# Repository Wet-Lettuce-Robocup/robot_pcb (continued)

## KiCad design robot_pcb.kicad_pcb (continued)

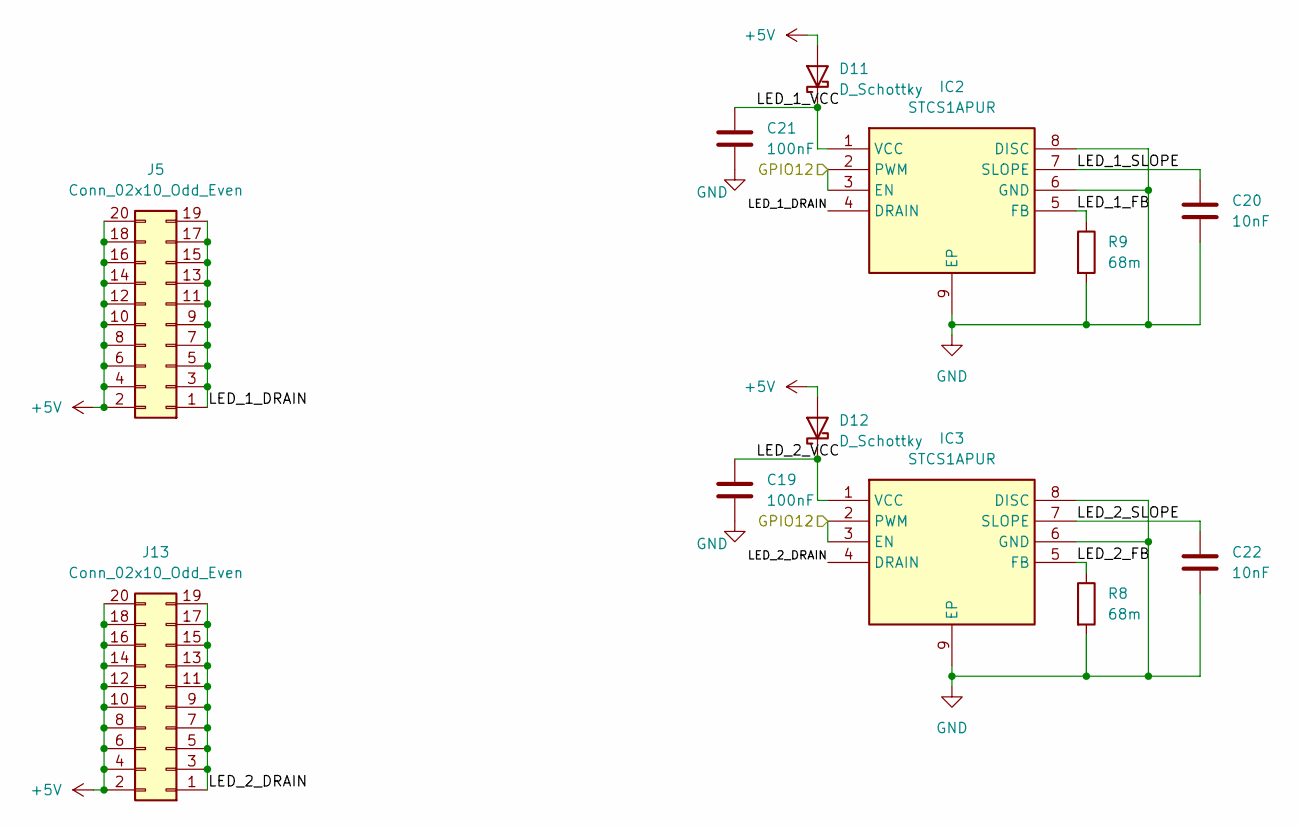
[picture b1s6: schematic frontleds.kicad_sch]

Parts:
C19, C21: 100nF; C_0402_1005Metric; LCSC C307331
C20, C22: 10nF; C_0402_1005Metric; LCSC C15195
D11, D12: D_Schottky; D_SOD-123; LCSC C83528
IC2, IC3: STCS1APUR; SON50P300X300X100-9N-D; Mouser Part Number 511-STCS1APUR
J5, J13: Conn_02x10_Odd_Even; Samtec_HSEC8-110-01-X-DV-A_2x10_P0.8mm_Socket_AlignmentPins; LCSC C4572809
R8, R9: 68m; R_0402_1005Metric; LCSC C728416

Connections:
+5V: D11.2 (A), D12.2 (A), J5.2, J5.4, J5.6, J5.8, J5.10, J5.12, J5.14, J5.16, J5.18, J5.20, J13.2, J13.4, J13.6, J13.8, J13.10, J13.12, J13.14, J13.16, J13.18, J13.20; also elsewhere on the board
/Front LEDs/GPIO12: IC2.2 (PWM), IC2.3 (EN), IC3.2 (PWM), IC3.3 (EN); also elsewhere on the board
/Front LEDs/LED_1_DRAIN: IC2.4 (DRAIN), J5.1, J5.3, J5.5, J5.7, J5.9, J5.11, J5.13, J5.15, J5.17, J5.19
/Front LEDs/LED_1_FB: IC2.5 (FB), R9.1
/Front LEDs/LED_1_SLOPE: C20.2, IC2.7 (SLOPE)
/Front LEDs/LED_1_VCC: C21.1, D11.1 (K), IC2.1 (VCC)
/Front LEDs/LED_2_DRAIN: IC3.4 (DRAIN), J13.1, J13.3, J13.5, J13.7, J13.9, J13.11, J13.13, J13.15, J13.17, J13.19
/Front LEDs/LED_2_FB: IC3.5 (FB), R8.1
/Front LEDs/LED_2_SLOPE: C22.1, IC3.7 (SLOPE)
/Front LEDs/LED_2_VCC: C19.1, D12.1 (K), IC3.1 (VCC)
GND: C19.2, C20.1, C21.2, C22.2, IC2.6 (GND), IC2.8 (DISC), IC2.9 (EP), IC3.6 (GND), IC3.8 (DISC), IC3.9 (EP), R8.2, R9.2; also elsewhere on the board

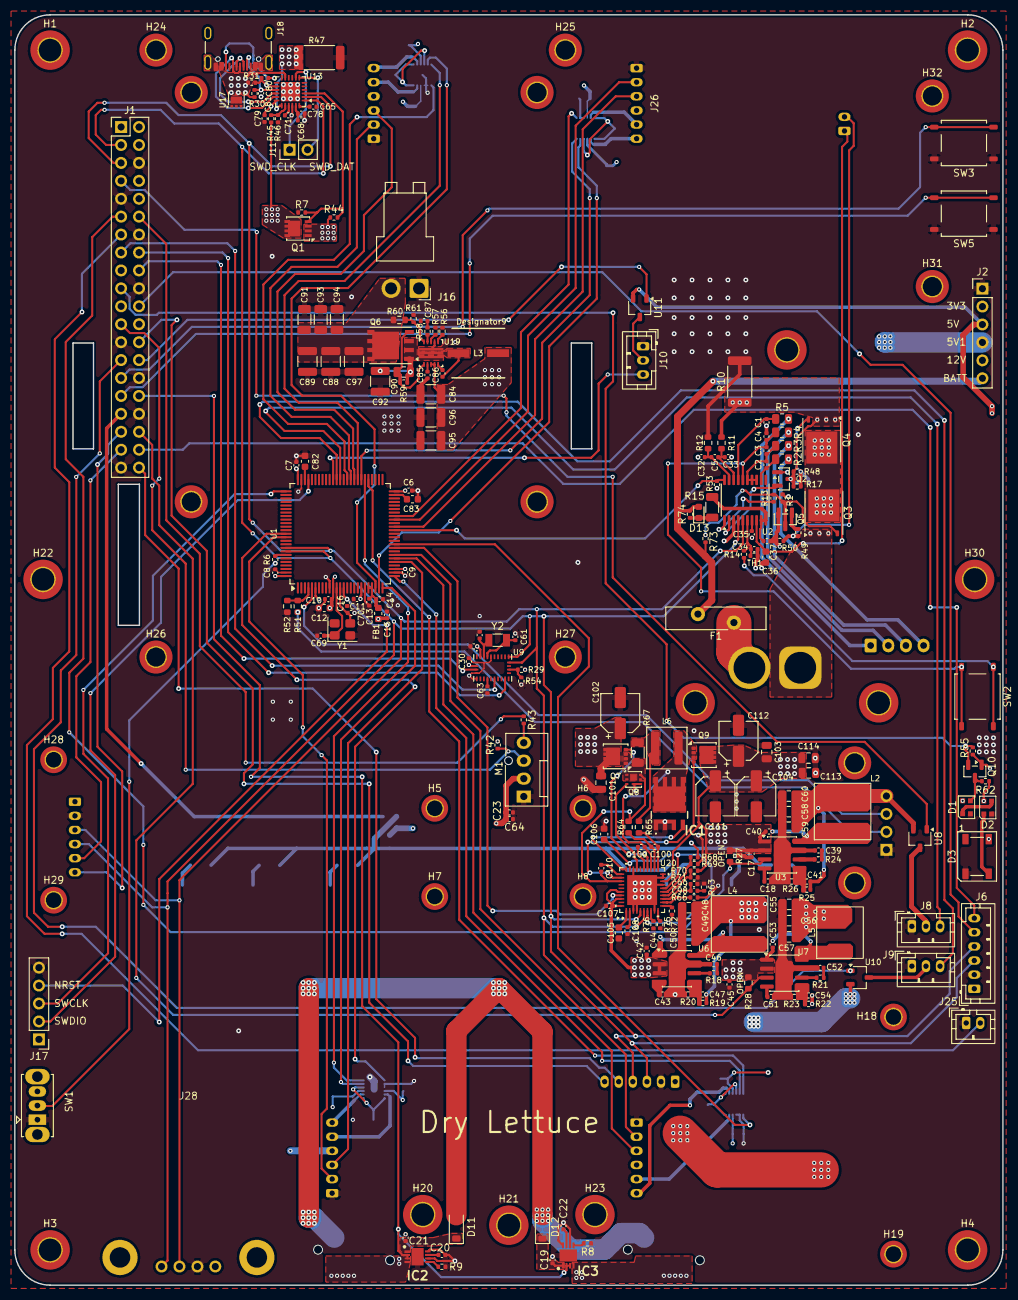
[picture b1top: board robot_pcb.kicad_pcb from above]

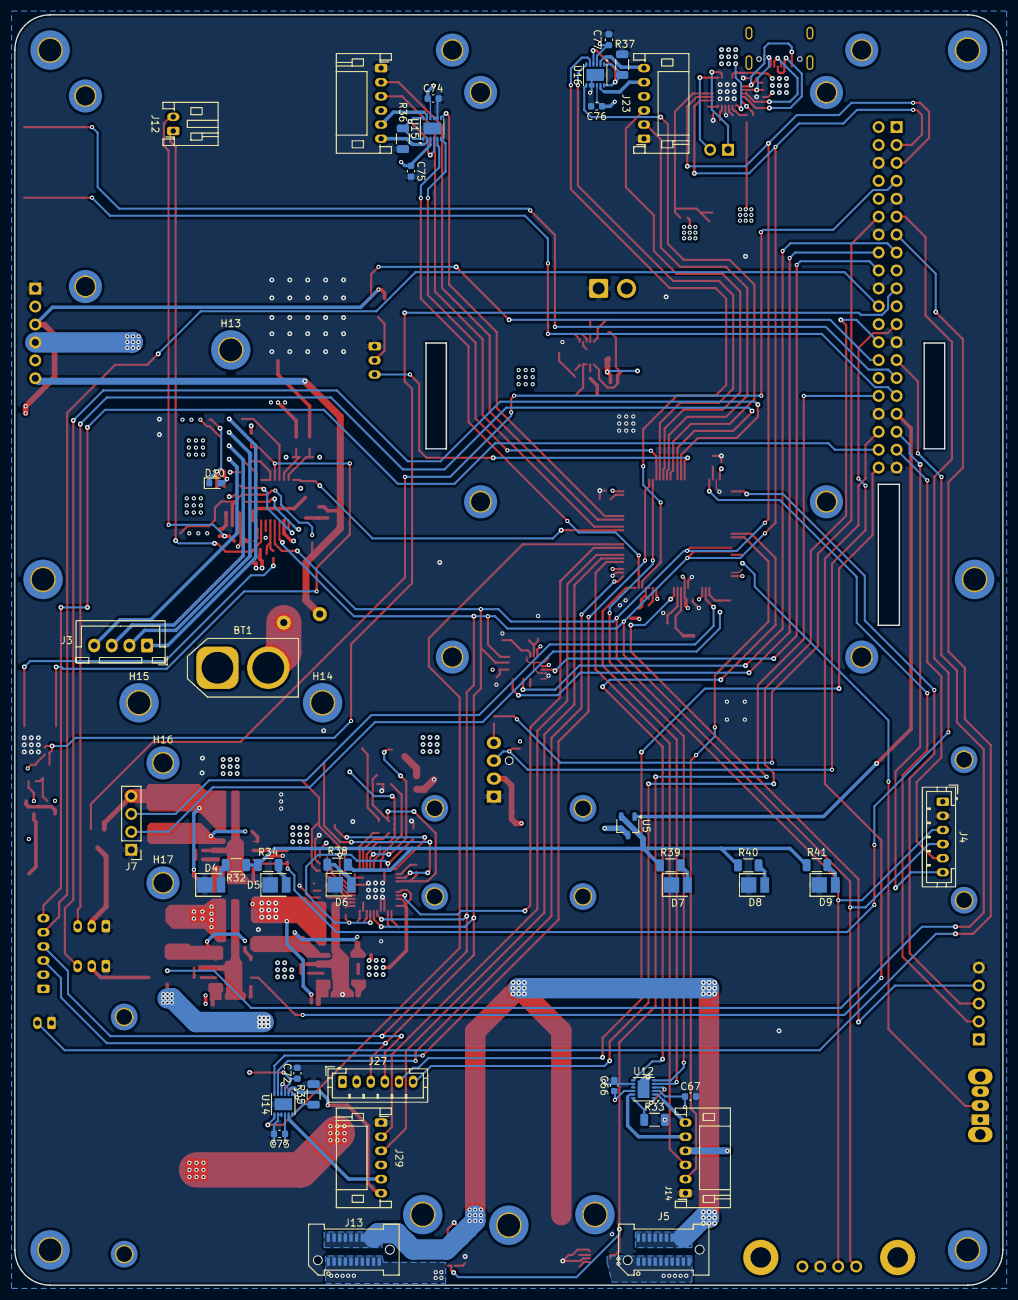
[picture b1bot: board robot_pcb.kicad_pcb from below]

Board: 4 copper layers, 140.0 x 180.0 mm, 297 parts (47 on the bottom side), 195 nets.

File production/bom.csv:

Designator,Footprint,Quantity,Value,LCSC Part #
BT1,AMASS_XT60-M_1x02_P7.20mm_Vertical,1,Battery,C98733
"C1, C14, C15, C2, C3, C4, C65, C68, C79",0402,9,1uF,C52923
"C10, C107, C109, C11, C110, C16, C19, C21, C23, C24, C30, C32, C33, C35, C40, C44, C5, C53, C6, C63, C64, C7, C71, C78, C8, C86, C9",0402,27,100nF,C307331
C100,0402,1,75pF,C107010
C101,0805,1,10uF,C2932476
C102,CP_Elec_5x5.9,1,27uF,C347564
"C103, C113, C114",0805,3,4.7uF,C98192
"C104, C111, C112",CP_Elec_5x5.9,3,56uF,C2162042
"C105, C106",0603,2,22uF,C2762594
"C108, C13, C18, C20, C22, C43, C51",0402,7,10nF,C15195
"C12, C38",0603,2,10uF,C96446
"C17, C42, C45",0402,3,10uF,C315248
C34,0402,1,4.7nF,C84705
C36,0603,1,4.7uF,C69335
C37,0402,1,2.2uF,C307418
"C39, C46, C52",0402,3,2.7nF,C84704
"C41, C47, C54",0402,3,47pF,C60137
"C48, C49, C50, C55, C56, C57, C58, C59, C60",0805,9,22uF,C602037
"C61, C62",0402,2,12pF,C76948
"C66, C72, C74, C76",0603,4,100nF,C14663
"C67, C73, C75, C77",0603,4,1uf,C29936
"C69, C70",0402,2,22pF,C76960
"C80, C81",0402,2,390pF,C114397
"C82, C83",0603,2,2.2uF,C23630
"C84, C95, C96",1210,3,22uF,C309062
C85,0402,1,4.7uF,C6119795
C87,0402,1,820pF,C107031
"C88, C89, C92, C97",1210,4,10uF,C138687
C90,0805,1,22nF,C107147
"C91, C93, C94",1206,3,4.7uF,C51205
C98,0402,1,47nF,C272875
C99,0402,1,100pF,C106200
"D1, D2",LED_WS2812B-2020_PLCC4_2.0x2.0mm,2,WS2812B-2020,C965555
D10,0603,1,D,C35621074
"D11, D12",D_SOD-123,2,D_Schottky,C83528
D3,LED_WS2812B_PLCC4_5.0x5.0mm_P3.2mm,1,WS2812B-V6,C52917433
"D4, D5, D6, D7, D8, D9",LED_PLCC_2835,6,LED,C2843876
F1,Fuse_Bourns_MF-RG900,1,Polyfuse,C3762600
FB1,0603,1,120R,C113030
IC1,IAUC120N06S5N011ATMA1,1,IAUCN04S7L028ATMA1,C29536843
"IC2, IC3",SON50P300X300X100-9N-D,2,STCS1APUR,C2971041
J1,PinHeader_2x20_P2.54mm_Vertical,1,Raspberry_Pi_2_3,C50980
J10,JST_PH_B3B-PH-K_1x03_P2.00mm_Vertical,1,Servo_TrayRelease,C158004
J11,PinHeader_1x02_P2.54mm_Vertical,1,Conn_01x02,C52016390
J12,JST_PH_S2B-PH-K_1x02_P2.00mm_Horizontal,1,Conn_01x02,C5251182
"J13, J5",Samtec_HSEC8-110-01-X-DV-A_2x10_P0.8mm_Socket_AlignmentPins,2,Conn_02x10_Odd_Even,C4572809
J14,JST_PH_S6B-PH-K_1x06_P2.00mm_Horizontal,1,Motor FR,C157920
J16,JST_VH_B2PS-VH_1x02_P3.96mm_Horizontal,1,19V Output,C158007
J17,PinHeader_1x05_P2.54mm_Vertical,1,Programmer,C42431835
J18,USB_C_Receptacle_GCT_USB4105-xx-A_16P_TopMnt_Horizontal,1,USB_C_Receptacle_USB2.0_16P,C3025063
J2,PinHeader_1x06_P2.54mm_Vertical,1,Power_Bypass,C52016393
J23,JST_PH_S6B-PH-K_1x06_P2.00mm_Horizontal,1,Motor BR,C157920
J25,JST_PH_B2B-PH-K_1x02_P2.00mm_Vertical,1,ConductClaw,C5251182
J26,JST_PH_S6B-PH-K_1x06_P2.00mm_Horizontal,1,Motor BL,C157920
J27,JST_PH_B6B-PH-K_1x06_P2.00mm_Vertical,1,TOF_Front,C495261
J28,OLED_small,1,OLED_Display,C2718488
J29,JST_PH_S6B-PH-K_1x06_P2.00mm_Horizontal,1,Motor FL,C157920
J3,JST_XH_B4B-XH-A_1x04_P2.50mm_Vertical,1,Lipo,C594232
J4,JST_PH_B6B-PH-K_1x06_P2.00mm_Vertical,1,TOF_Right,C495261
J6,JST_PH_B6B-PH-K_1x06_P2.00mm_Vertical,1,TOF_Claw,C495261
J7,PinHeader_1x04_P2.54mm_Vertical,1,UltraS_Side,C52016392
J8,JST_PH_B3B-PH-K_1x03_P2.00mm_Vertical,1,Servo_Grab,C158004
J9,JST_PH_B3B-PH-K_1x03_P2.00mm_Vertical,1,Servo_Lift,C158004
"L2, L4",NRS8040T3R6NJGJ,2,3.6uH,C223037
L3,INDM7570X400N,1,1.4uH,C41239516
L5,CYA0630-3.3uH,1,3.3uH,C5189747
L6,L_Coilcraft_XAL5030-XXX,1,600nH,C19191623
M1,FanPinHeader_1x04_P2.54mm_Vertical,1,Fan_Tacho_PWM,C240840
Q1,Vishay_PowerPAK_1212-8_Single,1,DI040P04PT-AQ,C6934675
"Q10, Q5",SOT-23,2,2N7002,C65189
Q2,SOT-23,1,AO3401A,C15127
"Q3, Q4",TDSON-8-1,2,CSD17578Q5A,C2871447
Q6,PowerPAK_SO-8_Single,1,Si7149DP,C553982
Q7,VSON-8_3.3x3.3mm_P0.65mm_NexFET,1,CSD17577Q3A,C201632
Q8,Texas_DQK,1,CSD17313Q2,C2863837
Q9,VSON-8_3.3x3.3mm_P0.65mm_NexFET,1,CSD17578Q3A,C205986
"R1, R13, R14, R29, R42, R48, R49, R55, R6, R62",0402,10,10k,C60490
"R10, R47",2512,2,5m,C2903482
"R11, R12",0603,2,100,C105588
R15,1206,1,100,C2907369
"R16, R2, R3, R4, R5",0805,5,100,C105577
"R17, R53",0402,2,1M,C138033
R18,0402,1,16k,C25759
R19,0402,1,118k,C852490
"R20, R23",0402,2,22.1k,C163478
R21,0402,1,10.5k,C5581335
R22,0402,1,69.8k,C852893
R24,0402,1,15.8k,C26956
R25,0402,1,105k,C171671
R26,0402,1,20k,C93942
"R32, R34, R38, R39, R40, R41",1206,6,91,C5842965
"R33, R35, R36, R37",1206,4,100m,C3033268
R43,0402,1,330,C105875
"R44, R50, R72",0402,3,100k,C60491
R45,0402,1,200k,C114763
R46,0402,1,68k,C137947
R51,0603,1,1k,C22548
R52,0603,1,2k,C105576
R56,0402,1,140k,C114151
R57,0402,1,68.1k,C11537
R58,0402,1,44.2k,C25895
R59,0402,1,309k,C4180598
R60,0603,1,1.2M,C13315
R61,0402,1,80.6k,C25921
R63,0402,1,3.65k,C852768
"R64, R65",0603,2,10,C109318
R66,0402,1,14.3k,C185465
R67,1206,1,2m,C2479048
"R68, R70",0402,2,61.9k,C852869
"R69, R71",0402,2,5.62k,C851068
R75,0402,1,40.2k,C137983
R76,0402,1,20.5k,C185445
"R8, R9",0402,2,68m,C728416
SW1,SW_Slide_SPDT_Straight_CK_OS102011MS2Q,1,SW_SPDT,C221829
SW2,SW_Push_1P1T_NO_CK_KSC6xxJ,1,SW_Push,C431539
"SW3, SW5",SW_Push_1P1T_NO_CK_KMR2,2,SW_Push,C51927445
TH1,0402,1,10k,C209959
U1,LQFP-100_14x14mm_P0.5mm,1,STM32F407VGTx,C720656
"U10, U11, U5, U8",TSOT-23,4,DMG2305UX-7,C150470
"U12, U14, U15, U16",Maxim_TDFN-12-1EP_3x3mm_P0.5mm_EP1.7x2.5mm,4,~,C194048
U13,QFN-24-1EP_4x4mm_P0.5mm_EP2.75x2.75mm,1,CYPD3175-24LQXQ,C2952419
U17,WSON-6-1EP_2x2mm_P0.65mm_EP1x1.6mm,1,TVS0500DRV,C609571
U19,RNW0013A,1,TPS611781RNWR,C2862009
U2,TSSOP-20_4.4x6.5mm_P0.65mm,1,BQ76920PW,C601650
U20,VQFN40_RHA_TEX,1,XLM51772RHAR,C41383743
"U3, U6, U7",SOIC-8-1EP_3.9x4.9mm_P1.27mm_EP2.29x3mm,3,AP64501SP-13,C2071517
U9,IC_BNO086,1,BNO086,C5264422
Y1,Crystal_SMD_3225-4Pin_3.2x2.5mm,1,25MHz,C5444544
Y2,Crystal_SMD_3215-2Pin_3.2x1.5mm,1,32.768KHz,C99010

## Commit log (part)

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2026-01-19 added empty sheets for each voltage regulator
2026-01-19 add components
2026-01-20 added custom symbols for motor connectors
2026-01-20 updated motor connector reference from u to j to match the fact that it is a connector
2026-01-20 added gitignore
2026-01-20 removed files ignored by gitignore
2026-01-20 added power circuitry to stm32
2026-01-20 added some pin definitions for stm32
2026-01-20 5vreg
2026-01-21 3v3 done
2026-01-21 added 12v circuit, no values yet
2026-01-21 added values
2026-01-21 bms nearly finished
2026-01-21 added polyfuse for added safety
2026-01-21 added pull down resistor to chg pin as it is not used
2026-01-21 bring back 3v3
2026-01-21 cleaning
2026-01-21 added separate ground for battery protection circuit
2026-01-21 sorry can ignore if u want
2026-01-21 re-added gnd1 to bms
2026-01-22 added labels to stm32 outputs
2026-01-22 created symbol and footprint for motor driver, and connected to stm32
2026-01-22 all one component?
2026-01-22 restored main file
2026-01-22 added debug output
2026-01-22 added usb c port
2026-01-22 remove 12V
2026-01-22 remove other
2026-01-22 regulators in one file
2026-01-22 leds
2026-01-23 cleaned up some sheet pins
2026-01-24 added footprints to all components in 12v regulator
2026-01-24 probably didn't need that many capacitors on the 12v output
2026-01-24 added more labels
2026-01-24 parts
2026-01-24 part numebrs
2026-01-25 added some footprints
2026-01-25 fixed lipo symbol
2026-01-25 fixed bad ground placement
2026-01-25 Added BNO086
2026-01-25 small changes
2026-01-27 added some more footprints
2026-02-01 regulators layout
2026-02-01 update regulators layout
2026-02-02 fixed whatever was going on with i2c
2026-02-02 added some more stuff to pcb
2026-02-02 working on stm32
2026-02-02 added footprints for almost everything
2026-02-02 mostly finished stm
2026-02-02 added schematics and footprints to project
2026-02-02 working on bms layout
2026-02-02 update inductor footprint to drylettuce library
2026-02-02 started routing one regulator
2026-02-02 finised layout for bms (no traces yet)
2026-02-02 this is probably better tbh
2026-02-02 12v regulator layout
2026-02-02 finished bno086 layout
2026-02-02 added some tracks
2026-02-02 fat traces
2026-02-02 made 12v inductor traces thicker
2026-02-02 removed random bit of copper
2026-02-02 flipped battery connectors
2026-02-03 added board outline
2026-02-03 moved some stuff to roughly where it will be
2026-02-03 idrk what i changed tbh but probably not anything important
2026-02-04 update pcb and schematic
2026-02-04 oled
2026-02-04 changed motor driver outline from margin to courtyard layer
2026-02-04 oled fix
2026-02-04 moving thjings around
2026-02-04 add holes
2026-02-04 updated drawing from fusion
2026-02-05 more moving
2026-02-06 need to do motor driver
2026-02-06 yeah idk what im doing someone fix
2026-02-06 learning kicad by making some holes
2026-02-07 added title to pcb schematic
2026-02-08 add driver symbol real
2026-02-08 motor drivers done
2026-02-09 added motor drivers and leds to pcb
2026-02-09 moved motor drivers around
2026-02-09 add inductor footprint
2026-02-09 routing voltage reguulators
2026-02-09 updated pcb
2026-02-10 wired up some motor drivers, idk if this is right tho
2026-02-10 changed switch footprint for stm32 boot0
2026-02-10 finished wiring motor drivers and moved boot button
2026-02-10 attempted to wire some stuff, its a bit of a mess tho feel free to delete
2026-02-11 route last regulator and changed ultrasonic connector
2026-02-11 add tofs
2026-02-11 moved a single resistor
2026-02-12 something changed maybe
2026-02-12 connected front motor drivers better
2026-02-12 wired motor drivers more
2026-02-12 stuff
2026-02-13 added a power plane thing for gnd1
2026-02-13 more routing
2026-02-13 wired everything else except for new tof sensors cos we might need a multiplexer idk
2026-02-13 removed redundant vias
2026-02-13 bro why did it do that i thought i fixed that anyway its fixed now
2026-02-13 Shifted whole pcb + connected tofs
    Hopefully pcb is aligned to the grid now. Somebody please check my wiring bc it's probably cooked but I gave it a go anyway.
2026-02-13 jetson holes
2026-02-13 Updated UserDrawings to add tof position and mounting holes
    Had to reroute some traces, should be fine
2026-02-13 cleaning up routing
2026-02-14 Added connector for PWM fan
    Tachometer -> PI GPIO11
    PWM -> PI PWM1
2026-02-14 12v Routing
2026-02-14 need to update servo mosfet
2026-02-14 probably fixed some drc violations
    also changed middle layers settings to be power instead of signal, i think thats useful?
2026-02-14 made gnd1 plane have priority over gnd
2026-02-14 routing
2026-02-14 error cleanup
2026-02-14 Added better power management for fan and adjusted tofs
    Probably broke something tbh. Added some resistors and a capacitor, changed tofs to actually be on the back layer lmao
2026-02-14 moved back motor drivers to bottom layer
2026-02-15 connected cc pins on usb c connector to 5.1v instead of 5v
2026-02-15 updated all footprints cos kicad was complaining hopefully that didn't break anything
2026-02-15 replaced some sketch connections in the 12v regulator with filled zones
2026-02-15 This footprint must have been autogenerated or something because there is NO WAY a sane human made it anyway fixed some stuff
2026-02-15 update mdriver pad
2026-02-15 fixed some errors an stuff
2026-02-16 i think its fine?
    @will-da-pro help
2026-02-16 pd controller started
2026-02-16 probably works
2026-02-16 work on pd ic
2026-02-16 idk it showed question marks again
2026-02-16 mounting holes for handle + updated pcb from sch
2026-02-17 added usb c thing to pcb
2026-02-17 actually connected the vias this time
2026-02-17 hopefully those can be left as nc unless google ai is gaslighting me
2026-02-17 huhhhhh
2026-02-17 fixed super cooked regulators
2026-02-18 fixed all unconnected items
2026-02-18 added more vias for power lines
2026-02-18 a 90º turn has been eliminated
2026-02-19 fixed usb c pd ic schematic
2026-02-19 added tvs diode to schematic of usb c port
2026-02-19 added new stuff to pcb
2026-02-19 changed some more values
2026-02-20 replaced mosfet for main power supply cos it was too overpowered
2026-02-20 added chg protection fet to BQ76920PW
2026-02-20 moved stuff
2026-02-20 kinda cooked kill switch but i think it should work
2026-02-20 if it's cooked but it works it's still cooked but at least it works
2026-02-20 aligned switch with mounting holes
2026-02-20 updated mounting hole footprints
2026-02-20 something changed
2026-02-20 moved one of the encoder traces cos it looks cleaner
2026-02-20 fixed silkscreen for usb controller and stm32
2026-02-20 fixed silkscreen for voltage regulators
2026-02-20 small changes to some label positions
2026-02-20 small change
2026-02-20 all drc errors gone, changed footprints
    some footprints were cooked so i just removed or moved stuff on the silkscreen layer of each footprint
2026-02-21 fixed some problems with stm32 capacitors
2026-02-21 connected side ultrasonic to stm32
2026-02-21 added resistor voltage divider for ultrasonic
2026-02-21 connected fault pins on motor drivers to stm32
2026-02-21 unfinished changes part 1
2026-02-21 moved kill-switch further back
2026-02-21 add frontleds
2026-02-22 finished adding front leds
    probably works idk
2026-02-24 added symbol and footprint for 19v regulator
2026-02-24 stuf w button
2026-02-24 more stuff with switches n things
2026-02-26 added schematic for 19v regulator (no footprints or values yet)
2026-02-26 added values to 19v reg components
2026-02-26 started adding 19v reg to pcb (unfinished)
2026-02-26 horizontal jst
2026-02-26 moved traces apart
2026-02-26 moved odometry over and increased distance between some traces
2026-02-26 wired front leds
2026-02-26 fixed ALL drc errors and warnings
2026-02-26 added labels to everything
2026-02-27 put in some vias so it looks a bit better with gnd plane
2026-02-27 landon
2026-02-27 bandon
2026-02-27 fixed a drc violation
2026-02-27 cleaned up some traces
2026-02-27 fixed some cooked traces
2026-02-27 more lcsc part labels for non generic components
2026-02-27 more vias
2026-02-28 added schematic for new 12v regulator (no footprints yet)
2026-02-28 added footprints for new 12v regulator
2026-02-28 finished routing for 12v regulator
2026-02-28 fixed silkscreen violations
2026-02-28 added 3d models for most components
2026-02-28 added lcsc part numbers for non trivial 12v components
2026-02-28 lcsc numbers for other regulators
2026-02-28 made one of the traces less ugly
2026-03-04 used vias in pads to make stuff more compact
2026-03-04 moved usb c port to edge
2026-03-04 probably should have checked clearance
2026-03-04 made traces much thicker for power
2026-03-05 converted some power traces to filled zones for better current capabilities
2026-03-06 made some traces go over multiple layers for better thermals
2026-03-09 Updated edge cuts and drawings from earlier fusion changes and moved traces accordingly
    Also fixed jst connectors
2026-03-10 disconnected back tof and rotated button
2026-03-11 started moving traces to be same distance apart to look cleaner
2026-03-12 more progress on cleaning up traces
2026-03-12 so close
2026-03-12 finished fixing trace spacing for all major lines
2026-03-13 hopefully this doesnt mess stuff up
2026-03-13 front led base layout done, should probably move resistors onto this board
2026-03-13 smol boi
2026-03-13 changed front leds to use dedicated led current drivers
2026-03-13 tied STCS1A en to pwm
2026-03-13 export steps
2026-03-14 moved polyfuse to positive side of battery
2026-03-14 small changes to leds
2026-03-14 step files
2026-03-14 moved front led connectors to underneath pcb
2026-03-14 increased width of motor power connectors
2026-03-14 added 3d model for polyfuse
2026-03-14 made led 3d model path relative
2026-03-14 cleaning up some zones
2026-03-14 very small change to some trace widths
2026-03-15 fixed some issues with crystals and other stuff
2026-03-15 replaced tht fets with smd ones in bms
2026-03-15 increased width of a power filled zone
2026-03-15 forgot to connect that lol
2026-03-16 more lcsc
2026-03-16 lcsc + changed footprint of a capacitor
2026-03-17 lcsc again
2026-03-17 lcsc resistors and capacitors done probably except the 67m one
2026-03-17 standardised components
2026-03-17 a resistor did a 180 somehow idk
2026-03-18 resolve multiple clearance errors
2026-03-18 standardised components, removing mixed values
2026-03-18 production update
2026-03-18 add bom etc
2026-03-18 made power traces on bms go over multiple layers for better thermals
2026-03-18 removed random bit sticking out from gnd1 power plane
2026-03-18 weird 5v zone
2026-03-18 ah yes thermals
2026-03-18 prod
2026-03-18 ok i think this is the last one
2026-03-18 final prod maybe??
2026-03-19 changed leds
2026-03-19 lcsc for 68m resistors
2026-03-19 another diode
2026-03-19 6 pin tof sensors
2026-03-19 ALL LCSC PARTS DONE
2026-03-19 some labels
2026-03-19 final countdown
2026-03-19 Production of leds and pcb
2026-03-19 changed mosfet lcsc part
2026-03-20 update prod
2026-03-20 screw holes for display
2026-03-20 those should be m2.5
2026-03-20 aligned motors
2026-03-23 made it not overwrite other changes
2026-03-23 gerber files
2026-03-23 updated pcb from schematic and it pulled some changes that idk if they are fine or not but anyway
2026-03-23 added label for nrst
2026-03-26 changed constraints to 0.16mm clearance for 2oz copper
2026-03-26 fixed 99% of drc errors instead of finishing english
2026-03-27 fixed wrong jst connector
2026-04-23 Marked 19V regulator as DNP to simplify next board iteration
2026-04-23 changes to fix broken stuff
2026-04-23 switch now bigger
2026-04-23 bro how does this work (fix led symbol footprint and model)
    idk why frontleds can use drylettuce symbols but not footprints/3d models liek whaaaaa
2026-04-23 Revert "pcb"
    This reverts commit 4408802fdc77718ad8d669ae9eabbe9d43823e20.
2026-04-23 fix pcb
2026-04-24 added history to gitignore
